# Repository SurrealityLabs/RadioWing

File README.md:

# RadioWing
AM/FM/SW receiver in a FeatherWing form factor

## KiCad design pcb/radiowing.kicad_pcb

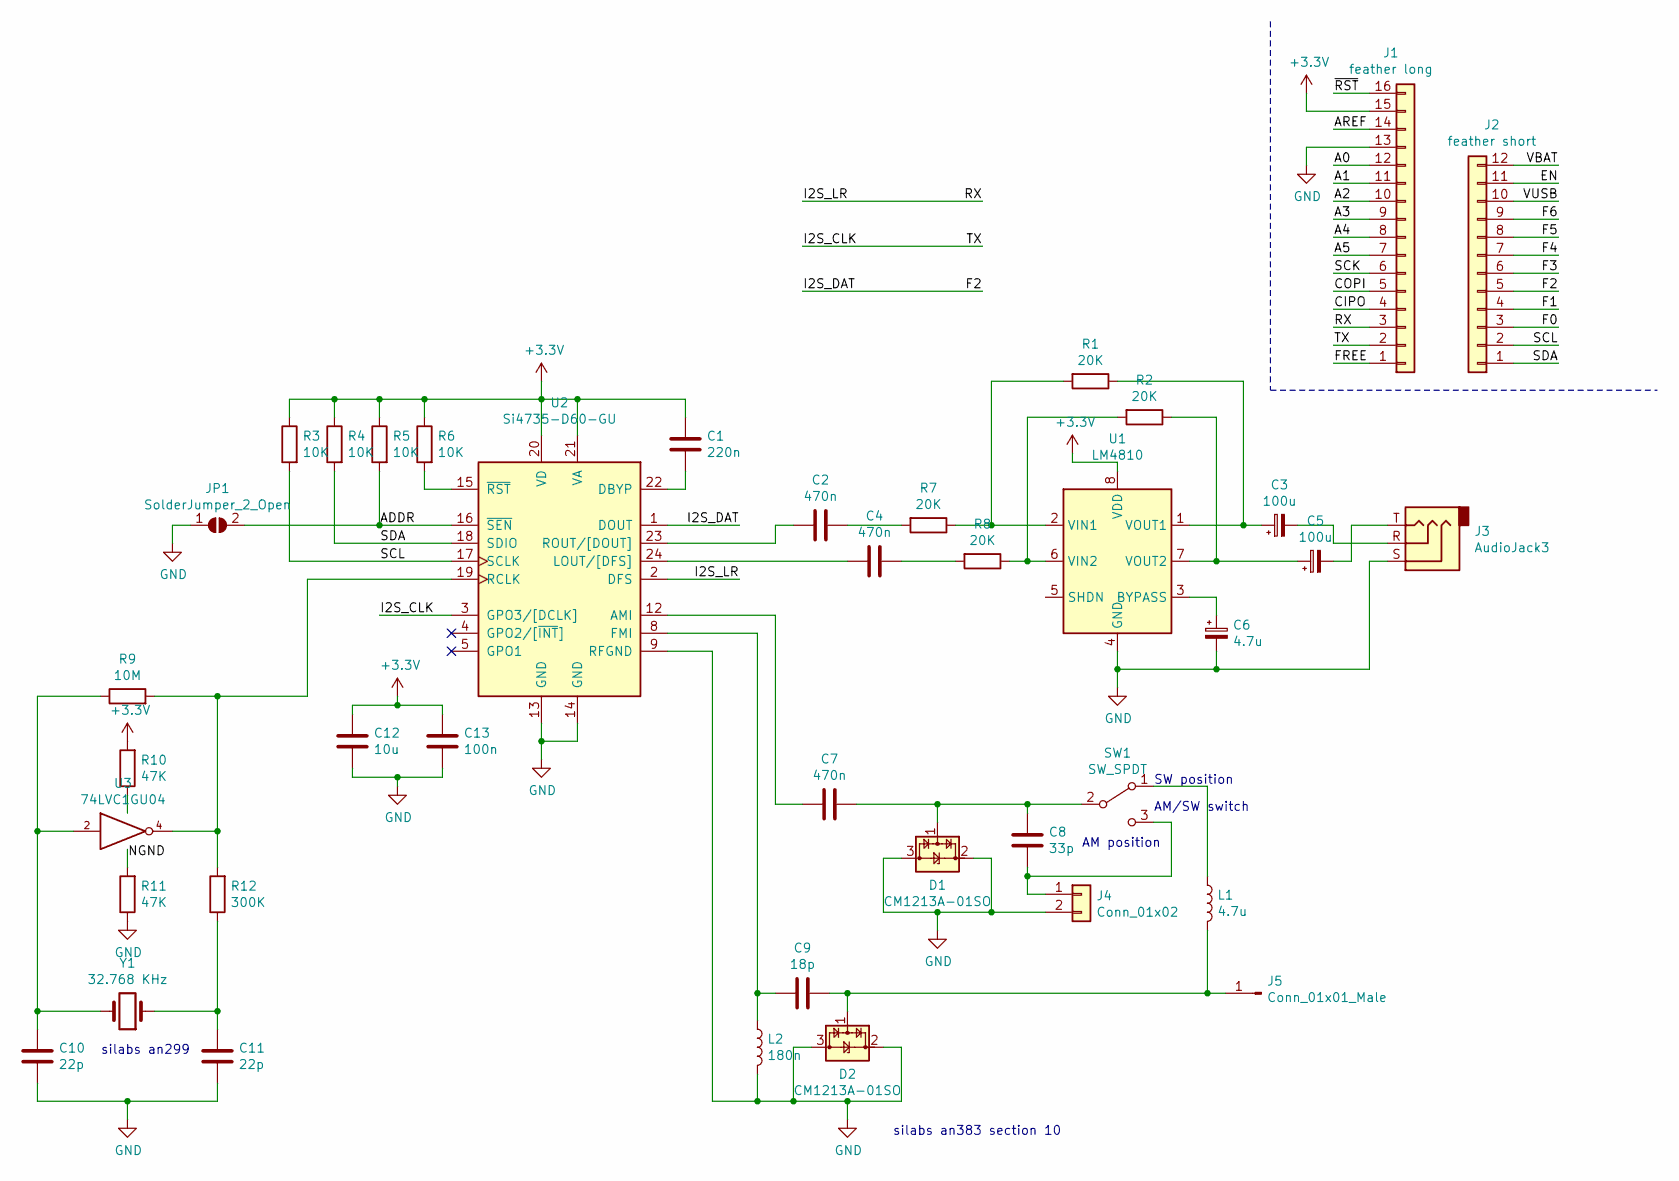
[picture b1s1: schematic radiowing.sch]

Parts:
C1: 220n; C_0603_1608Metric
C2, C4, C7: 470n; C_0603_1608Metric
C3, C5: 100u; CP_Elec_5x5.3
C6: 4.7u; CP_Elec_5x5.3
C8: 33p; C_0603_1608Metric
C9: 18p; C_0603_1608Metric
C10, C11: 22p; C_0603_1608Metric
C12: 10u; C_0805_2012Metric
C13: 100n; C_0603_1608Metric
D1, D2: CM1213A-01SO; SOT-23
J1: feather long; PinHeader_1x16_P2.54mm_Vertical
J2: feather short; PinHeader_1x12_P2.54mm_Vertical
J3: AudioJack3; Jack_3.5mm_CUI_SJ-3523-SMT_Horizontal
J4: Conn_01x02; PinHeader_1x02_P2.54mm_Vertical
J5: Conn_01x01_Male; PinHeader_1x01_P2.54mm_Vertical
JP1: SolderJumper_2_Open; SolderJumper-2_P1.3mm_Open_Pad1.0x1.5mm
L1: 4.7u; L_1008_2520Metric
L2: 180n; L_0603_1608Metric
R1, R2, R7, R8: 20K; R_0603_1608Metric
R3, R4, R5, R6: 10K; R_0603_1608Metric
R9: 10M; R_0603_1608Metric
R10, R11: 47K; R_0603_1608Metric
R12: 300K; R_0603_1608Metric
SW1: SW_SPDT; SW_SPDT_PCM12
U1: LM4810; TSSOP-8_3x3mm_P0.65mm
U2: Si4735-D60-GU; SSOP-24_3.9x8.7mm_P0.635mm
U3: 74LVC1GU04; SOT-23-5
Y1: 32.768 KHz; Crystal_DS26_D2.0mm_L6.0mm_Horizontal; Part ECS-.327-12.5-13

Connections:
+3V3: C1.1, C12.1, C13.1, J1.15, R3.1, R4.1, R5.1, R6.1, R10.2, U1.8 (VDD), U2.20 (VD), U2.21 (VA)
/A0: J1.12
/A1: J1.11
/A2: J1.10
/A3: J1.9
/A4: J1.8
/A5: J1.7
/ADDR: JP1.2 (B), R5.2, U2.16 (~SEN)
/AREF: J1.14
/CIPO: J1.4
/COPI: J1.5
/EN: J2.11
/F0: J2.3
/F1: J2.4
/F2: J2.5, U2.1 (DOUT)
/F3: J2.6
/F4: J2.7
/F5: J2.8
/F6: J2.9
/FREE: J1.1
/I2S_CLK: J1.2, U2.3 (GPO3/[DCLK])
/I2S_LR: J1.3, U2.2 (DFS)
/SCK: J1.6
/SCL: J2.2, R3.2, U2.17 (SCLK)
/SDA: J2.1, R4.2, U2.18 (SDIO)
/VBAT: J2.12
/VUSB: J2.10
/~RST: J1.16
unnamed: C1.2, U2.22 (DBYP)
unnamed: C2.1, R7.2
unnamed: C2.2, U2.23 (ROUT/[DOUT])
unnamed: C3.1, R1.1, U1.1 (VOUT1)
unnamed: C3.2, J3.R
unnamed: C4.1, R8.2
unnamed: C4.2, U2.24 (LOUT/[DFS])
unnamed: C5.1, R2.1, U1.7 (VOUT2)
unnamed: C5.2, J3.T
unnamed: C6.1, U1.3 (BYPASS)
unnamed: C7.1, C8.1, D1.1 (CH1), SW1.2 (B)
unnamed: C7.2, U2.12 (AMI)
unnamed: C8.2, J4.1, SW1.3 (C)
unnamed: C9.1, L2.1, U2.8 (FMI)
unnamed: C9.2, D2.1 (CH1), J5.1, L1.2
unnamed: C10.2, R9.1, U3.2, Y1.2
unnamed: C11.2, R12.1, Y1.1
unnamed: L1.1, SW1.1 (A)
unnamed: R1.2, R7.1, U1.2 (VIN1)
unnamed: R2.2, R8.1, U1.6 (VIN2)
unnamed: R6.2, U2.15 (~RST)
unnamed: R9.2, R12.2, U2.19 (RCLK), U3.4
VCC: R10.1, U3.5 (VCC)

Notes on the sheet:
silabs an299
silabs an383 section 10
AM/SW switch
AM position
SW position

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
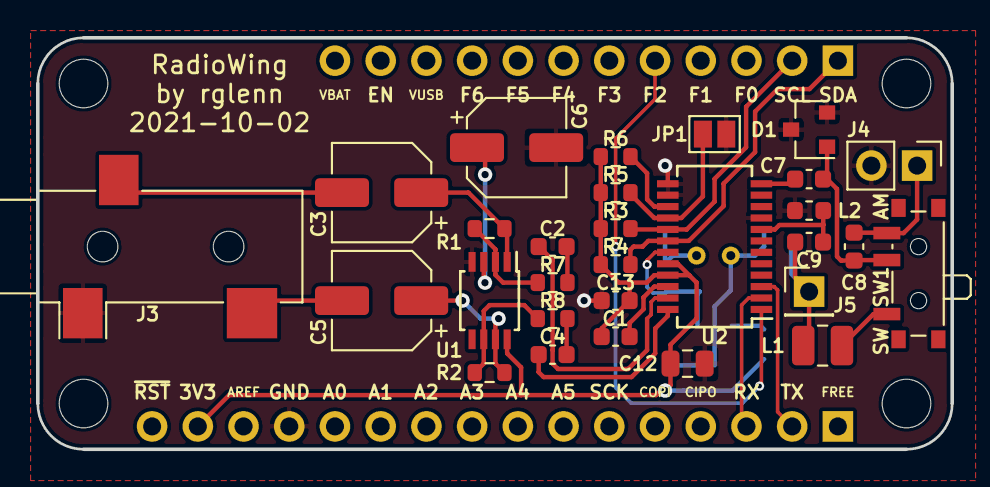
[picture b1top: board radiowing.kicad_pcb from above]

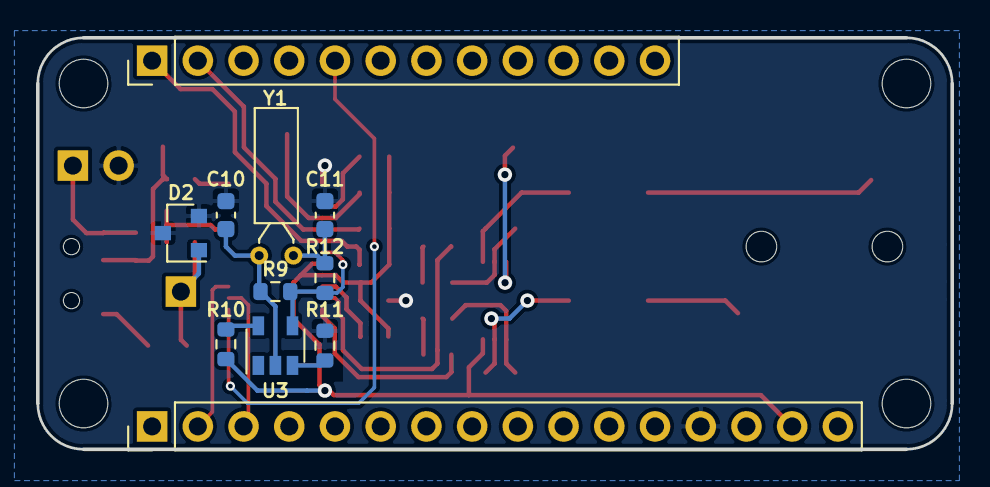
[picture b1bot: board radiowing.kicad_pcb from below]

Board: 2 copper layers, 50.8 x 22.9 mm, 40 parts (11 on the bottom side), 31 nets.

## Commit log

2021-10-03 Initial checkin
